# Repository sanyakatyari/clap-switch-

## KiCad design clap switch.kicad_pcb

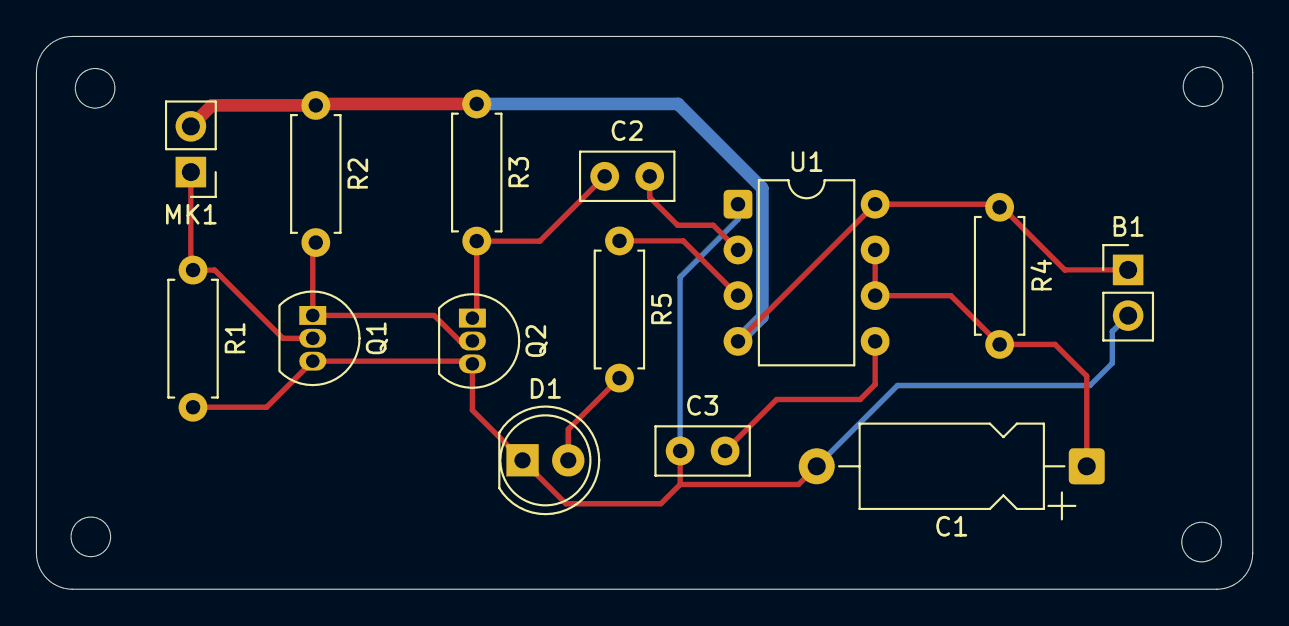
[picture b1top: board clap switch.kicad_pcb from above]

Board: 2 copper layers, 67.6 x 30.7 mm, 14 parts (0 on the bottom side), 10 nets.

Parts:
B1: 6V; PinHeader_1x02_P2.54mm_Vertical
C1: 100uF; CP_Axial_L10.0mm_D4.5mm_P15.00mm_Horizontal
C2, C3: 0.1uF; C_Disc_D5.0mm_W2.5mm_P2.50mm
D1: LED; LED_D5.0mm
MK1: PinHeader_1x02_P2.54mm_Vertical
Q1, Q2: BC547; TO-92_Inline
R1: 4.7K; R_Axial_DIN0207_L6.3mm_D2.5mm_P7.62mm_Horizontal
R2: 1K; R_Axial_DIN0207_L6.3mm_D2.5mm_P7.62mm_Horizontal
R3: 470; R_Axial_DIN0207_L6.3mm_D2.5mm_P7.62mm_Horizontal
R4: 10K; R_Axial_DIN0207_L6.3mm_D2.5mm_P7.62mm_Horizontal
R5: 330; R_Axial_DIN0207_L6.3mm_D2.5mm_P7.62mm_Horizontal
U1: NE555P; DIP-8_W7.62mm

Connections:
GND: B1.2 (-), C1.2, C3.1, D1.1 (K), Q1.3 (E), Q2.3 (E), R1.2, U1.1 (GND)
unnamed: B1.1 (+), MK1.2 (+), R2.1, R3.1, R4.1, U1.4 (~RST), U1.8 (VCC)
unnamed: D1.2 (A), R5.2
unnamed: MK1.1 (-), Q1.2 (B), R1.1
unnamed: Q1.1 (C), Q2.2 (B), R2.2
unnamed: C2.1, Q2.1 (C), R3.2
unnamed: C3.2, U1.5 (CONT)
unnamed: C1.1, R4.2, U1.6 (THRES), U1.7 (DISCH)
unnamed: R5.1, U1.3 (OUT)
unnamed: C2.2, U1.2 (TRIG)
